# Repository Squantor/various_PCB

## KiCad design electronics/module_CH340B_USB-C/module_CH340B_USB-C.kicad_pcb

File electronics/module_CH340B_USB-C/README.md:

# CH340B module
Module for the CH340B USB to serial converter using a USB-C connector.
## TODO's
Still some things need to be done:
* Review with one night in between
* Produce at [OSHPARK](https://oshpark.com/)
* Assemble
* Test & characterise
* update Readme.md with pictures and BOM
## BOM
* [USB-C connector from LCSC PCB cutout](https://lcsc.com/product-detail/USB-Connectors_Korean-Hroparts-Elec-TYPE-C-31-M-12_C165948.html)

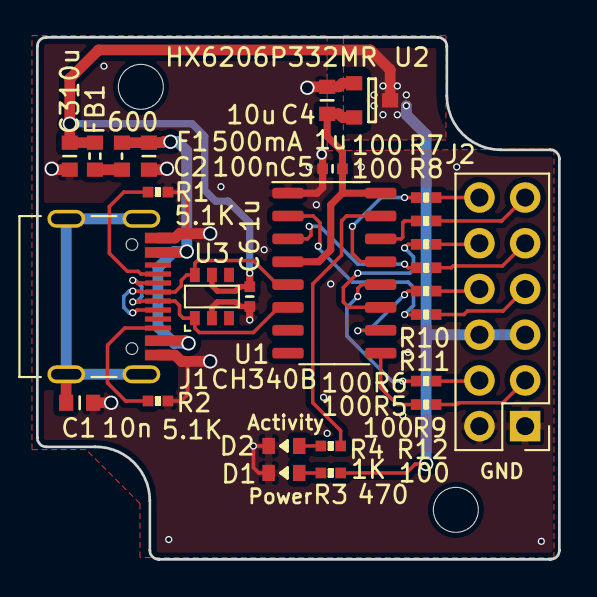
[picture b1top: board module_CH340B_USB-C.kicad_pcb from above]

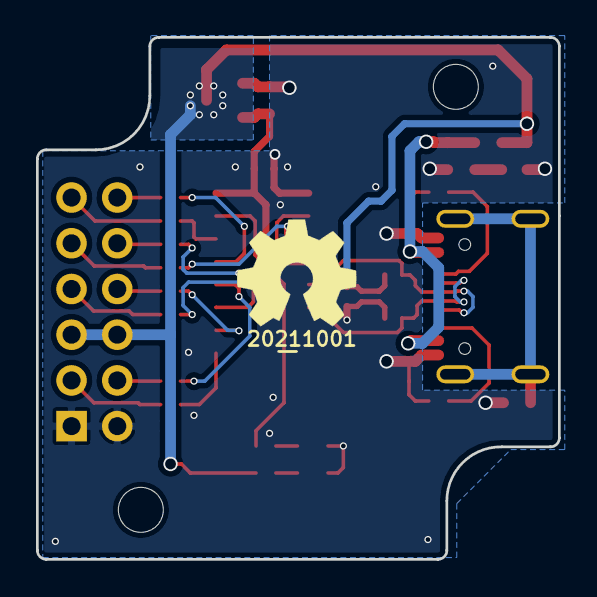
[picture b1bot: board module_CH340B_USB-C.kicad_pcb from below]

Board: 2 copper layers, 29.0 x 29.0 mm, 31 parts (2 on the bottom side), 29 nets.

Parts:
C1: 10n; C_0603
C2: 100n; C_0603
C3, C4: 10u; C_0603
C5, C6: 1u; C_0402
D1, D2: LED; LED_0603_hand
F1: 500mA; F_0603_hand
FB1: 600; L_0603
H1, H2: Drill_Hole_no_metal; MountingHole_2.5mm_no_metal
J1: USB-C_PD_USB; USB-C-HRO-31-M-12
J2: Conn_02x06_Odd_Even; PinHeader_2x06_P2.54mm_Vertical
N1: OHWLOGO; OSHW-Symbol_6.7x6mm_SilkScreen
N2: 20211001; Label_Generic
R1, R2: 5.1K; R_0402_hand
R3: 470; R_0402_hand
R4: 1K; R_0402_hand
R5, R6, R7, R8, R9, R10, R11, R12: 100; R_0402_hand
U1: CH340B; SO-16_3.9x9.9mm_P1.27mm
U2: HX6206P332MR; SOT23-3
U3: TVS_4_Array; SOT26-diodesinc

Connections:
/+3.3V: C4.2, C5.1, U1.4, U1.16, U2.2
/+5V: C3.1, C6.2, FB1.1, J2.5, J2.6, R3.1, U2.3, U3.5
/CC1: J1.A5, R1.2
/CC2: J1.B5, R2.2
/CTS: R12.2, U1.9
/DCD: R9.1, U1.12
/DN: J1.A7, J1.B7, U1.6, U3.1
/DP: J1.A6, J1.B6, U1.5, U3.6
/DSR: R11.1, U1.10
/DTR: R8.1, U1.13
/GND: C1.2, C2.2, C3.2, C4.1, C5.2, C6.1, D1.1, D2.1, J1.A1B12, J1.B1A12, J2.1, J2.2, R1.1, R2.1, U1.1, U2.1, U3.2
/RI: R10.1, U1.11
/RTS: R7.2, U1.14
/RXD: R6.2, U1.3
/TNOW: R4.1, U1.15
/TXD: R5.2, U1.2
/VBUS: C2.1, F1.2, J1.A4B9, J1.B4A9
unnamed: C1.1, J1.S
unnamed: D1.2, R3.2
unnamed: D2.2, R4.2
unnamed: F1.1, FB1.2
unnamed: J2.3, R12.1
unnamed: J2.4, R9.2
unnamed: J2.7, R5.1
unnamed: J2.8, R11.2
unnamed: J2.9, R6.1
unnamed: J2.10, R10.2
unnamed: J2.11, R7.1
unnamed: J2.12, R8.2

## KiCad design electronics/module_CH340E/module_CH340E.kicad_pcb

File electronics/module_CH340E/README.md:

# Jiangsu Qin Heng CH340E module
Module board for the [CH340E](http://www.wch.cn/product/CH340.html) USB to serial converter. Advantage of the CH340E is its compact size and low cost, requiring a minimum of additional components.
## TODO's
Still some things need to be done:
* schematic entry
* PCB layout
* Review with one night in between
* Produce at [OSHPARK](https://oshpark.com/)
* Assemble
* Test & characterise
* update Readme.md with pictures and BOM
## BOM
The CH340E is available from various chinese shops but can also be found on [LCSC](https://lcsc.com/).
* CH340E, [C99652 from LCSC](https://lcsc.com/product-detail/USB_CH340E_C99652.html)
# Pictures

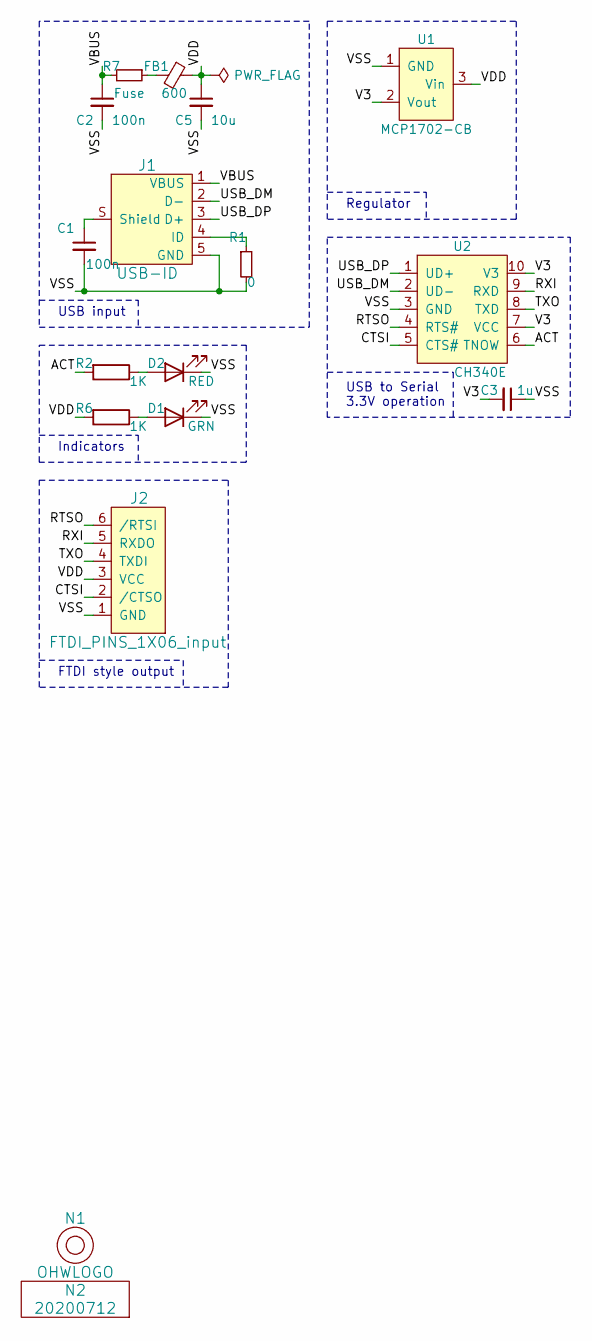
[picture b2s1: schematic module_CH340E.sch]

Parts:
C1: 100n; C_0805
C2: 100n; C_0603
C3: 1u; C_0603
C5: 10u; C_0805
D1: GRN; LED_0603_hand
D2: RED; LED_0603_hand
FB1: 600; R_0603_hand
J1: USB-ID; USB-muB-SMD_TH
J2: FTDI_PINS_1X06_input; PinHeader_1x06_P2.54mm_Vertical
N1: OHWLOGO; OSHW-Symbol_6.7x6mm_SilkScreen
N2: 20200712; Label_Generic
R1: 0; R_0603_hand
R2, R6: 1K; R_0603_hand
R7: Fuse; R_0603_hand
U1: MCP1702-CB; SOT23-3-Microchip-TT
U2: CH340E; MSOP-10

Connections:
/ACT: R2.2, U2.6 (TNOW)
/CTSI: J2.2 (/CTSO), U2.5 (CTS#)
/RTSO: J2.6 (/RTSI), U2.4 (RTS#)
/RXI: J2.5 (RXDO), U2.9 (RXD)
/TXO: J2.4 (TXDI), U2.8 (TXD)
/USB_DM: J1.2 (D-), U2.2 (UD-)
/USB_DP: J1.3 (D+), U2.1 (UD+)
/V3: C3.2, U1.2 (Vout), U2.7 (VCC), U2.10 (V3)
/VBUS: C2.1, J1.1 (VBUS), R7.2
/VDD: C5.1, FB1.1, J2.3 (VCC), R6.2, U1.3 (Vin)
/VSS: C1.2, C2.2, C3.1, C5.2, D1.1 (K), D2.1 (K), J1.5 (GND), J2.1 (GND), R1.2, U1.1 (GND), U2.3 (GND)
unnamed: C1.1, J1.S (Shield)
unnamed: D1.2 (A), R6.1
unnamed: D2.2 (A), R2.1
unnamed: FB1.2, R7.1
unnamed: J1.4 (ID), R1.1

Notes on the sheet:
USB input
Regulator
Indicators
USB to Serial 3.3V operation
FTDI style output

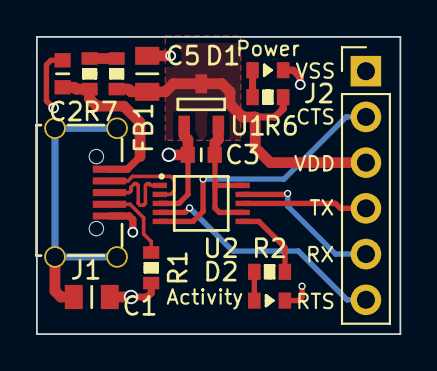
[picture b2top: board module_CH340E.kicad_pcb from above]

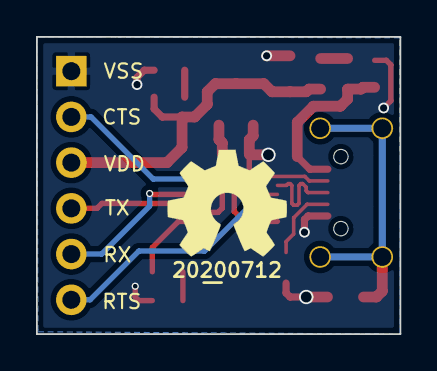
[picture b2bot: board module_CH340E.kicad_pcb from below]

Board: 2 copper layers, 20.2 x 16.5 mm, 17 parts (2 on the bottom side), 16 nets.

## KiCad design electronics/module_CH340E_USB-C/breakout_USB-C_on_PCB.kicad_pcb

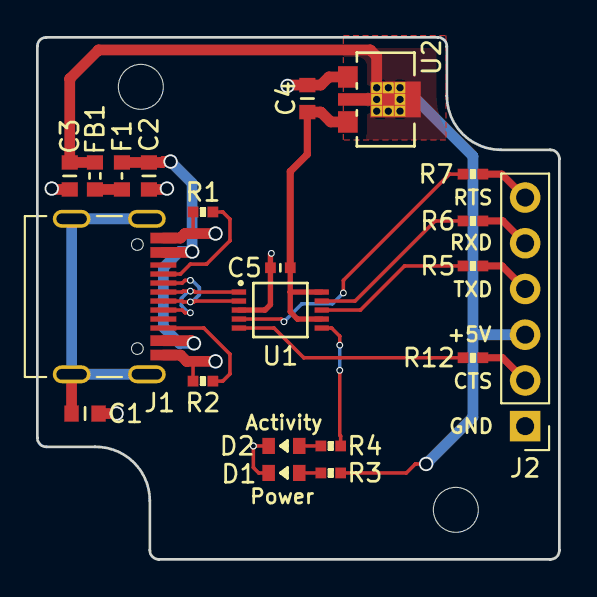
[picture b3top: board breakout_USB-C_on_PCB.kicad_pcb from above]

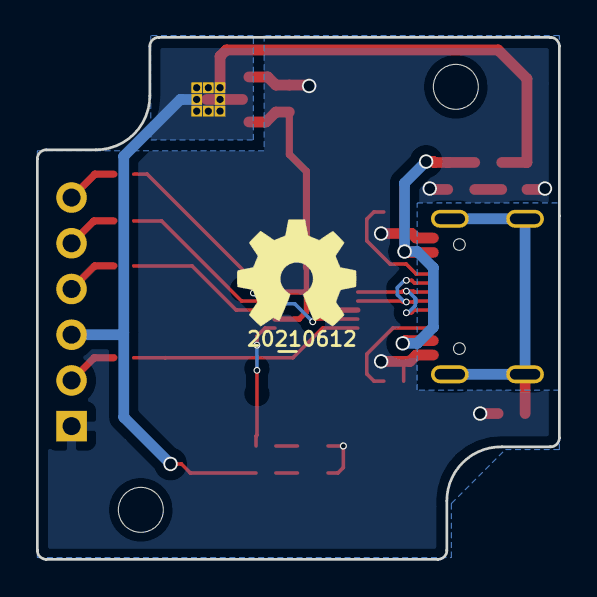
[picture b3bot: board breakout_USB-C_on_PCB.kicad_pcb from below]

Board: 2 copper layers, 29.0 x 29.0 mm, 25 parts (2 on the bottom side), 21 nets.

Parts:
C1: 10n; C_0603
C2: 100n; C_0603
C3, C4: 10u; C_0603
C5: 1u; C_0402
D1, D2: LED; LED_0603_hand
F1: 500mA; F_0603_hand
FB1: 600; L_0603
H1, H2: Drill_Hole_no_metal; MountingHole_2.5mm_no_metal
J1: USB-C_PD_USB; USB-C-HRO-31-M-12
J2: Conn_02x06_Odd_Even; PinHeader_1x06_P2.54mm_Vertical
N1: OHWLOGO; OSHW-Symbol_6.7x6mm_SilkScreen
N2: 20210612; Label_Generic
R1, R2: 5.1K; R_0402_hand
R3: 470; R_0402_hand
R4: 1K; R_0402_hand
R5, R6, R7, R12: 100; R_0402_hand
U1: CH340E; MSOP-10
U2: MCP1702-MB; SOT89-SOT23-Dual-NXP

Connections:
/+3.3V: C4.2, C5.1, U1.7, U1.10, U2.3
/+5V: C3.1, FB1.1, J2.3, R3.1, U2.2
/CC1: J1.A5, R1.2
/CC2: J1.B5, R2.2
/CTS: R12.2, U1.5
/DN: J1.A7, J1.B7, U1.2
/DP: J1.A6, J1.B6, U1.1
/GND: C1.2, C2.2, C3.2, C4.1, C5.2, D1.1, D2.1, J1.A1B12, J1.B1A12, J2.1, R1.1, R2.1, U1.3, U2.1
/RTS: R7.2, U1.4
/RXD: R6.2, U1.9
/TNOW: R4.1, U1.6
/TXD: R5.2, U1.8
/VBUS: C2.1, F1.2, J1.A4B9, J1.B4A9
unnamed: C1.1, J1.S
unnamed: D1.2, R3.2
unnamed: D2.2, R4.2
unnamed: F1.1, FB1.2
unnamed: J2.2, R12.1
unnamed: J2.4, R5.1
unnamed: J2.5, R6.1
unnamed: J2.6, R7.1

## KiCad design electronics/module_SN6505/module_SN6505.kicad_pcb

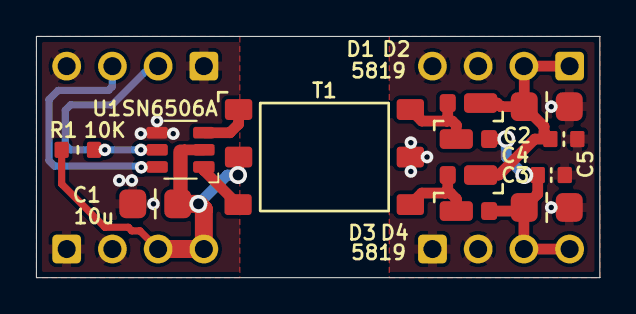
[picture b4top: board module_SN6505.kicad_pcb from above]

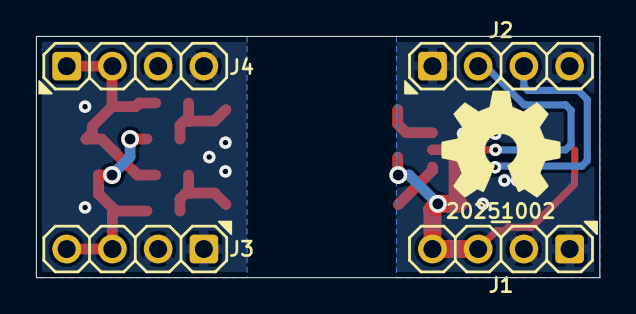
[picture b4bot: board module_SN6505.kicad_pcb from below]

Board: 2 copper layers, 31.3 x 13.4 mm, 18 parts (6 on the bottom side), 11 nets.

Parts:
C1, C2, C3: 10u; C_1206_0805
C4, C5: 1u; C_0603
D1, D2, D3, D4: 5819; SOD-323HE-shikues
J1, J2, J3, J4: Conn_01x04; Header-0254-1X04-H010
N1: 20251002; Label_Generic
N2: OHWLOGO; OSHW-Symbol_6.7x6mm_SilkScreen
R1: 10K; R_0603_hand
T1: STR7040; T-3_8W-6Pin_hand
U1: SN6506A; SOT23-6-TI

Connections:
/Enable: J2.2, R1.2, U1.5 (EN)
/ExtClk: J2.3, U1.6 (CLK)
/P1: T1.3 (N1_3), U1.1 (D1)
/P2: T1.1 (N1_1), U1.3 (D2)
/VIN: C1.2, J1.3, J1.4, R1.1, T1.2 (N1_2), U1.2 (VCC)
/VOUT+: C2.1, C5.1, D1.1 (K), D3.1 (K), J4.1, J4.2
/VOUT-: C3.1, C4.1, D2.2 (A), D4.2 (A), J3.3, J3.4
GND: C1.1, J1.1, J1.2, J2.1, J2.4, U1.4 (GND)
GND1: C2.2, C3.2, C4.2, C5.2, J3.1, J3.2, J4.3, J4.4, T1.5 (N2_2)
unnamed: D1.2 (A), D2.1 (K), T1.6 (N2_1)
unnamed: D3.2 (A), D4.1 (K), T1.4 (N2_3)

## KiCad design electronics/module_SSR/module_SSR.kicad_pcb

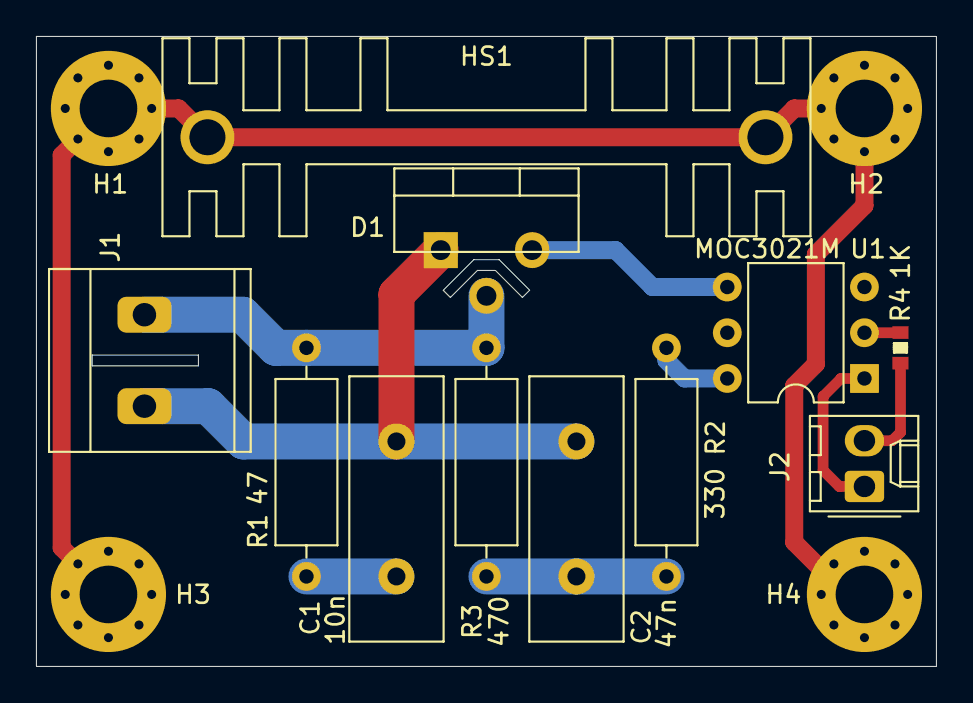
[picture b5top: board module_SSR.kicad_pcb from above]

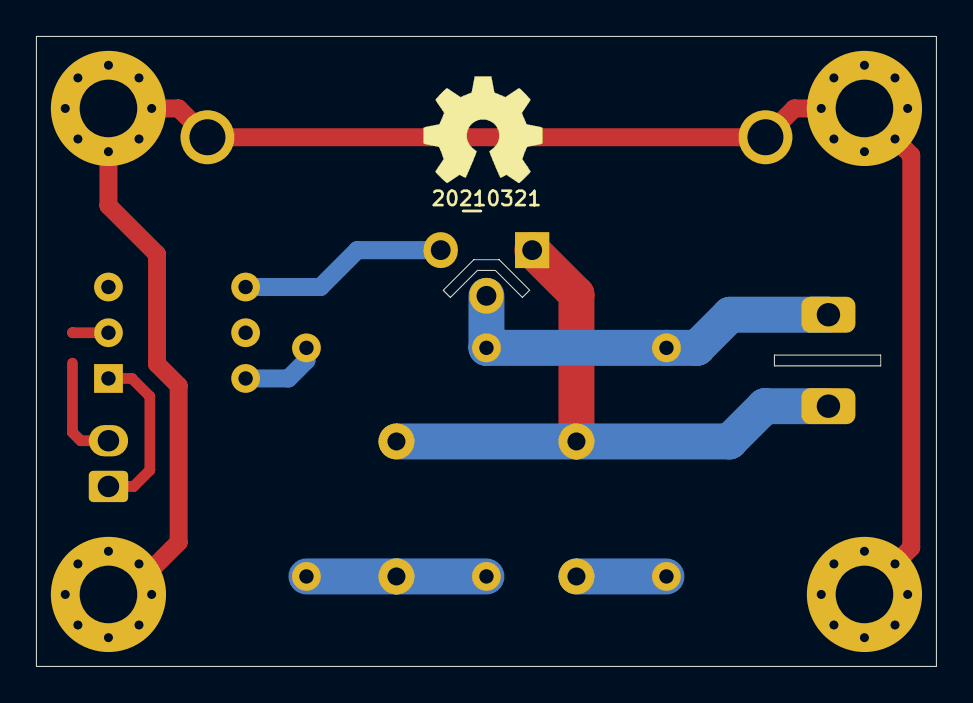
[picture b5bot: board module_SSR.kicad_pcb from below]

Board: 2 copper layers, 50.0 x 35.0 mm, 17 parts (2 on the bottom side), 10 nets.

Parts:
C1: 10n; C_Disc_D14.5mm_W5.0mm_P7.50mm
C2: 47n; C_Disc_D14.5mm_W5.0mm_P7.50mm
D1: BTA16-600CRG; TO-220-3_Vertical_stagger
H1, H2, H3, H4: M3; MountingHole_3.2mm_M3_Pad_Via
HS1: XSD683-022
J1: Conn_01x02; MKDS_2conn_508pitch_1711725
J2: Conn_01x02; Molex_KK-254_AE-6410-02A_1x02_P2.54mm_Vertical
N1: 20210321; Label_Generic
N2: OHWLOGO; OSHW-Symbol_6.7x6mm_SilkScreen
R1: 47; R_Axial_DIN0309_L9.0mm_D3.2mm_P12.70mm_Horizontal
R2: 330; R_Axial_DIN0309_L9.0mm_D3.2mm_P12.70mm_Horizontal
R3: 470; R_Axial_DIN0309_L9.0mm_D3.2mm_P12.70mm_Horizontal
R4: 1K; R_0603_hand
U1: MOC3021M; DIP-6_W7.62mm

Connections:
/LED_A: J2.1, U1.1
/LED_C: J2.2, R4.2
/LIVE: D1.2, J1.1, R1.1, R3.1
/SWITCH: C1.2, C2.2, D1.1, J1.2
Earth: H1.1, H2.1, H3.1, H4.1, HS1.1, HS1.2
unnamed: C1.1, R1.2
unnamed: C2.1, R2.2, R3.2
unnamed: D1.3, U1.4
unnamed: R2.1, U1.6
unnamed: R4.1, U1.2
